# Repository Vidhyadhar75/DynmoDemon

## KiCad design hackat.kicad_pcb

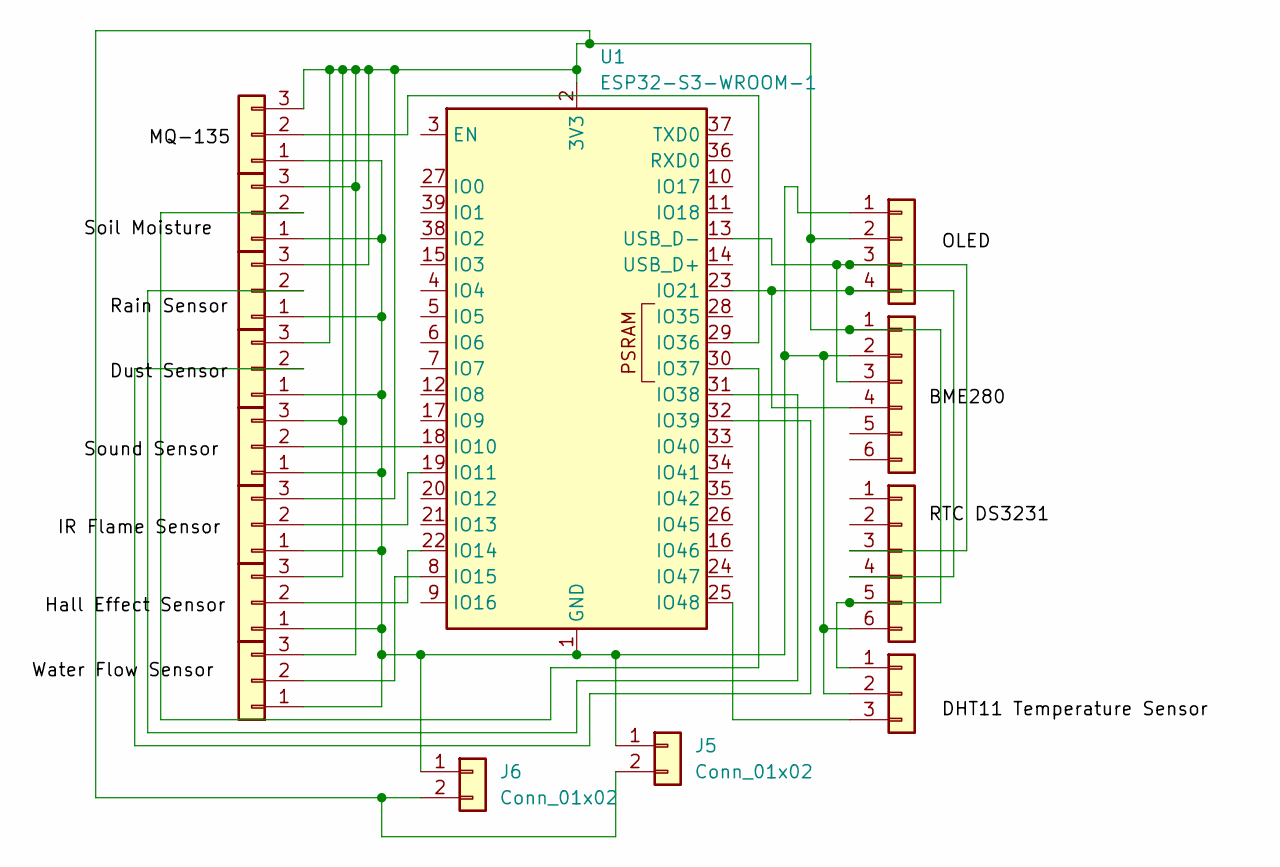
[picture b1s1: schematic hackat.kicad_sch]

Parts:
J2: Conn_01x04; PinHeader_1x04_P1.00mm_Vertical
J3, J4: Conn_01x06; PinHeader_1x06_P1.00mm_Vertical
J5, J6: Conn_01x02; PinHeader_1x02_P1.00mm_Vertical
J7, J8, J9, J10, J11, J12, J13, J16, J17: Conn_01x03; PinHeader_1x03_P1.00mm_Vertical
U1: ESP32-S3-WROOM-1

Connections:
unnamed 2: J2.3, J3.3, J4.3, U1.13 (USB_D-); also elsewhere on the board
unnamed: J2.4, J3.4, J4.4, U1.23 (IO21)
unnamed: J7.2, U1.32 (IO39)
unnamed: J8.2, U1.31 (IO38)
unnamed: J9.2, U1.30 (IO37)
unnamed: J2.1, J3.2, J4.6, J5.1, J6.1, J7.1, J8.1, J9.1, J10.1, J11.1, J12.1, J13.1, J16.1, J17.2, U1.1 (GND), U1.40 (GND), U1.41 (GND)
unnamed: J10.2, U1.29 (IO36)
unnamed: J2.2, J3.1, J4.5, J5.2, J6.2, J7.3, J8.3, J9.3, J10.3, J11.3, J12.3, J13.3, J16.3, J17.1, U1.2 (3V3)
unnamed: J11.2, U1.18 (IO10)
unnamed: J12.2, U1.19 (IO11)
unnamed: J13.2, U1.22 (IO14)
unnamed: J16.2, U1.8 (IO15)
unnamed: J17.3, U1.25 (IO48)

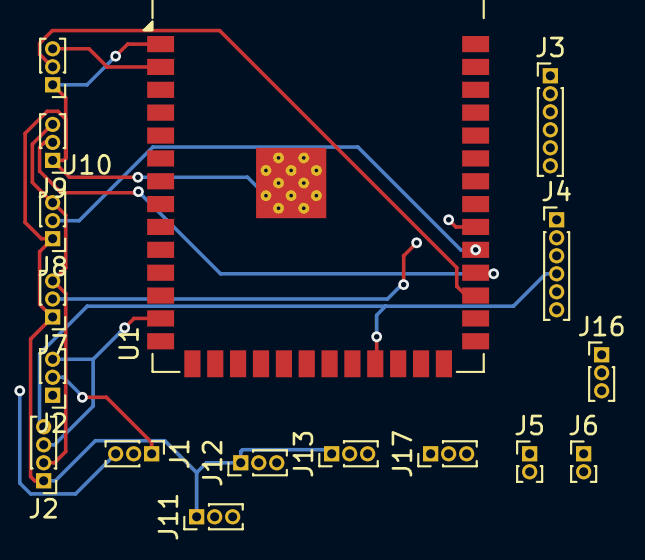
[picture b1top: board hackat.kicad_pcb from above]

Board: 2 copper layers, 17 parts (0 on the bottom side), 15 nets.

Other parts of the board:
J1: Conn_01x03; PinHeader_1x03_P1.00mm_Vertical
J2#2: Conn_01x04; PinHeader_1x03_P1.00mm_Vertical

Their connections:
unnamed: J1.1, J2#2.2
unnamed: J1.3, J2#2.1
unnamed 2: J2#2.3; also elsewhere on the board
